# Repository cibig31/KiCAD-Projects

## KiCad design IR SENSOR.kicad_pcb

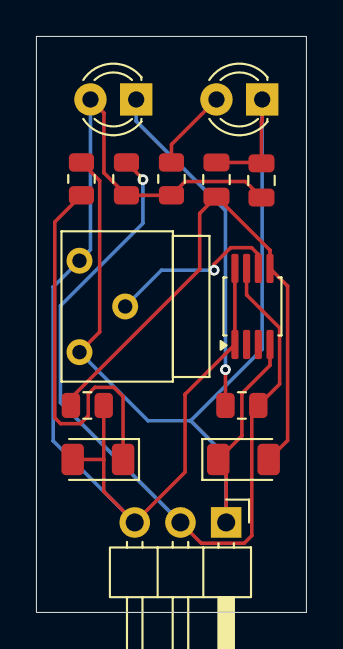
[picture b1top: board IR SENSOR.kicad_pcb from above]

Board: 2 copper layers, 15.0 x 32.0 mm, 14 parts (0 on the bottom side), 8 nets.

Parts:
C1, C2: C; C_0805_2012Metric
D1, D4: LED; LED_1206_3216Metric
D2: IR204A; LED_D3.0mm_IRBlack
D3: LED; LED_D3.0mm
J1: Conn_01x03_Pin; PinHeader_1x03_P2.54mm_Horizontal
R1, R2, R3, R4, R5: R; R_0805_2012Metric
RV1: R_Potentiometer; Potentiometer_Bourns_3339W_Horizontal
U1: LTC6752xMS8-2; MSOP-8_3x3mm_P0.65mm

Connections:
+5V: C1.1, D1.2 (A), D3.2 (A), J1.3, R2.1, R3.1, R4.1, RV1.1, U1.1 (VCC), U1.8 (VDD)
Earth: C1.2, C2.2, D2.1 (K), D4.1 (K), J1.1, R1.2, RV1.3, U1.4 (~SHDN)
unnamed: D1.1 (K), R1.1
unnamed: D2.2 (A), R3.2
unnamed: D3.1 (K), R5.1
unnamed: C2.1, D4.2 (A), R4.2, U1.5 (~LE)
unnamed: J1.2, R2.2, R5.2, U1.7
unnamed: RV1.2, U1.6 (VEE)
